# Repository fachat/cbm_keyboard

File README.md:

# Commodore PET keyboards

Note: this is a part of a larger set of repositories, with [upet_family](https://github.com/fachat/upet_family) as the main repository.

This is part of a re-incarnation of the Commodore PET computer(s) from the later 1970s.

This repo shows how to build a keyboard for the Commodore PET, mainly for my own re-incarnation, but potentially for original PET as well (untested).

Keyboards can be seen in the PETindex [keyboard section](http://www.6502.org/users/andre/petindex/keyboards.html).

## N-Type

This keyboard is the typewriter-stlye keyboard used in most 40 column models, except for the originals with the chicklet keyboard.

### PCB

#### Open source PCB by Steve Gray

For my builds I started by using the N-type keyboard PCB by Steve Gray from his [MX replacement keyboards projects](http://cbmsteve.ca/mxkeyboards/index.html)
As Steve only has the PCB, I designed a 3D-printable base support for the PCB.
It is available on tinkercad and the STL files are also available here.

Based on that I created a new R3 version of the board that includes options for
backlit LEDs and keyboard controllers allowing key re-mapping independent from
the PET's own editor ROM. You can find it in [PET-N](PET-N)

NOTE: In R3.0A you need to fix some things:

1. Connect the V33 and VCC33 lines - basically the oscillator for the Atmega controllers does not have power, so that needs to be supplied.
2. There is an off-by-one error on the row multiplexer. It has rows R0-9, while the keys are connected to R1-10. For now you have to connect R0 and R10, and fix the issue in the controller software.

In the current R3.0B these two fixes have been applied, but the actual PCB is not tested yet (and probably never will). A future 3.1 fix this for good.

### Programming the R3 PCB

The R3 PCB has (optionally) two Atmega32a microcontrollers on board, that implement two functions:

1. mapping keys between the keyboard and the host 
2. controlling the LEDs.

To program the Microcontrollers you need an AVR programming tool like the AVRisp MkII that I use, or similar, that can program via the SPI interface (plus Reset) on the 6 pin programming header (which exists separately for each of the two Microcontrollers)

Both microcontrollers are connected to the I2C bus on the extended UPET keyboard interface.

#### Functions of the keyboard controller

Currently the keyboard controller maps the keys 1:1 from the keyboard matrix to the host keyboard interface.

In addition it sends the pressed keys (hardware key index) via I2C to address 0x10 (which is the LED controller).

Also, the keyboard mapping has these options:

1. direct mapping - each key is directly mapped to the corresponding host key
2. The top row of characters is remapped from the PET-N's characters (like $, %, etc) to the digits you'd normally expect in this place. The original chars are available with Shift, the originally shifted characters are available with Ctrl.

Note that in the future more mappings may be implemented.

Selection of the mapping is done by pressing the SRQ key a few seconds long. The keyboard will then send a menu text to the host that instructs the user how to switch the mapping.
It is best if the menu is triggered e.g. on the BASIC prompt.

The mapping is stored in the Atmega's EEPROM, and thus retained when the machine is switched off.

#### Functions of the LED controller

The LED controller listens on the I2C address 0x10 for commands.

With these commands you can set the constant value of each key LED, but also trigger certain programs that involve either a single key, or multiple keys.
For single keys you can let the colour slowly get dimmer until the LED is off, and then optionally restart with the original value.

The DILUTE program tries to do a simulated flow of the colour from the given key to the surrounding keys. It is not as good and smooth as it could be as the 
Atmega lacks memory to store the required precision of colour values.

The LOGO just sends the logo onto the keypad, and then lets it decay.

```
        // single LED programs. Followed by index, three colours, and a parameter
        LP_CONST        = 0,    // constant value, using the three parameters as RGB
        LP_LINDECAY     = 1,    // linear decay (note may change hue while getting lower)
        LP_LINDECAYLOOP = 2,    // linear decay with restart

        // single command program
        SP_KEYPRESS     = 64,   // just followed by the index to indicate a pressed key

        // multi-key programs
        KP_DILUTE       = 128,  // set initial value to given params, then let it flow off 
        KP_LOGO         = 129,  // C= logo on the keypad
```

All commands except KEYPRESS expect the key index, three colours, and a parameter after the command, i.e. six bytes in total.
KEYPRESS only has the index and thus requires only two bytes.

### Supports for PCB

The PCB needs some kind of support to be mounted into the PET or the Ulti-/Micro-PET cases.
There are two versions for Steve's and my derived PCB, the first one for the extended
that caters for the different connector, and the one better suitable for the original
PCB.

* [New support structure extended PET-N keyboard](https://www.tinkercad.com/things/2KwSQVdno7K-sjg-keybd-full-support-r1)
* [left part of the support](PET-Keyboard-Support-SJG-N-R1-left.stl)
* [right part of the support](PET-Keyboard-Support-SJG-N-R1-right.stl)

* [support structure for Steve's N-type keyboard at tinkercad](https://www.tinkercad.com/things/cUVlushPB3j-sjg-keybd-full-support-v07).
* [left part of the support](PET-Keyboard-Support-SJG-N-v07-left.stl)
* [right part of the support](PET-Keyboard-Support-SJG-N-v07-right.stl)

#### Texelec Petskey keyboard

This is the PET N-type keyboard available from Texelec.

As this is the PCB only, I have created a support structure for this too. Note, however, as I now prefer Steve's PCB, I only have an old version of the supports on tinkercad.

Two of each of these supports make up a keyboard base plate, where you only need to clip in the PCB for the keyboard with the mounted key switches. Then they have about the same dimensions as a C64 keyboard, and you can use them on top of the C64 keyboard support stands.

* [Petskey 1.0 keyboard on Texelec](https://texelec.com/product/petskey/)
* [Petskey support on tinkercad](https://www.tinkercad.com/things/5lenSoehSRu-petskey-full-support-plate)

### Key caps

There are two options, either use standard key caps, or 3D-printed ones.

#### Standard Keycaps

As, for the self-built keyboards from option 1 or 2 some standard MX switches are used, standard
key caps can be used as well. There is one caveat, however.

Newer key caps typically have a different inclination for each row of keys, that is the angle of the top key surface against the horizontal
is different for each row. This is to facilitate easier typing. In fact even the C64 keyboard has this.
The old PET keyboards, however, have the same angle - which is not zero! - for all rows. This makes it easier to use the same cap (in terms of physical dimensions)
on all rows, and just print on a different character for each key. Read more on those [key profiles](https://switchandclick.com/sa-vs-dsa-vs-oem-vs-cherry-vs-xda-keycap-profiles/).

I used two type of standard key caps:

1. [XDA profile, unmarked](https://www.amazon.de/gp/product/B06XSHK528/): this set of key caps does not have a print on it, and all keys have the same angle - zero. So it is
possible to use any of the key caps in any row. Which is important, as you need a specific number of keys for each key width.
Also, this set has space bars in different lengths, and there is one that fits the 6.25 character wide space bar for the petskey and sjg keyboards.
For the markings I just used a pen...

2. This one [Glorious PC Gaming Race ABS Doubleshot black, ANSI layout GAKC-045](https://www.caseking.de/glorious-pc-gaming-race-abs-doubleshot-schwarz-ansi-us-layout-gakc-045.html) I actually bought more or less
by accident. I only noticed that it has different angles per row when I tried it out. However, with the amount of caps I was able to only
use a wrong angle on Shift Lock, left Shift, Return and "4" - but it's barely noticable.
For the markings I used template from Steve's page, printed it on sticky paper, cut it out and glued it on the keys where the original did not fit.

#### Printed Keycaps

As a third option I used 3-D printed key caps that I designed myself.

The keycaps are made of three parts each:
1) a key form created by a parametric generator,
2) the top character print, extruded from the key form,
3) the front character (mostly the shifted character), extruded from the key form.

I created all parts, and integrated them in the [Tinkercad](https://tinkercad.com) web tool.

The key form is created using OpenSCAD by a [parametric generator](https://www.thingiverse.com/thing:2783650) (by Thingieverse user rsheldiii, published under the [CC BY-SA 3.0](https://creativecommons.org/licenses/by-sa/3.0/) license). Here is the [parameter file](keycaps/key_cbm3_customizer.scad). Only the key width needs to be adapted, and the inversion of the top for the space key.

Most of the top character prints are made from a [Microgramm font](https://www.wfonts.com/font/microgramma), converted to SVG using the [Font Squirrel](https://www.fontsquirrel.com/tools/webfont-generator) web page.

Some top characters, and especially the top words ("SHIFT", "RUN STOP" etc) are taken from [Steve's github page](https://github.com/sjgray/CBM-MX-Keyboards/tree/master/stickers). As SVG exported from inkscape did not work when imported
into tinkercad, I had to make screenshots from each character, and convert these screenshots into SVGs using this [online converter](https://image.online-convert.com/convert-to-svg).

The front characters are all from an [SVG file from wikipedia](https://en.wikipedia.org/wiki/Commodore_PET#/media/File:PET_Keyboard_improved.svg), from which I also took screenshots and converted to SVG as above.

You can find an oder version of the the STL files [here](keycaps/), in four parts due to its size. The current version is linked from tinkercad below.
Please note that it took me about 100+ hours just to print the full set of keys on my Snapmaker printer in high quality.
After printing you have to remove the supports that anchor the stem to the outside of the keycaps so it does
not break away when printing.

For your convenience there is an open project at PCBWay to print the key caps, see the links.

* [Keycaps for resin printing](https://www.tinkercad.com/things/7a94wJbLJPW-commodore-pet-caps-for-n-type-ulti-keyboard-resin?sharecode=oM7332wY6SwB6DUj0fZoZttCZ-khZDpZEqtmBmInKJo)
* [Master file for keycaps](https://www.tinkercad.com/things/clKxMCUccgg-master-commodore-pet-caps-for-n-ulti-keyboard-support-cuts)
[//] # * [Open project at PCBWay 3D printing](https://www.pcbway.com/project/shareproject/Commodore_PET_N_type_keycaps_c1c2d1a0.html)

### Switches

The PCBs work with standard Cherry-type/-compatible switches. I only tested Cherry brand switches, though. You may select depending on your preference regarding force needed, click noise etc.

I found the MX1A-C1NW a good compromise for me.

* [Cherry MX1A-C1NW at Mouser](https://www.mouser.de/ProductDetail/540-MX1A-C1NW)

## Gallery

 Assembled keyboard with white resin printed caps, with key prints painted with black alcohol ink
 Assembled keyboard with black PLA printed caps, with key prints painted with white alcohol ink
 Assembled keyboard with black PLA printed caps

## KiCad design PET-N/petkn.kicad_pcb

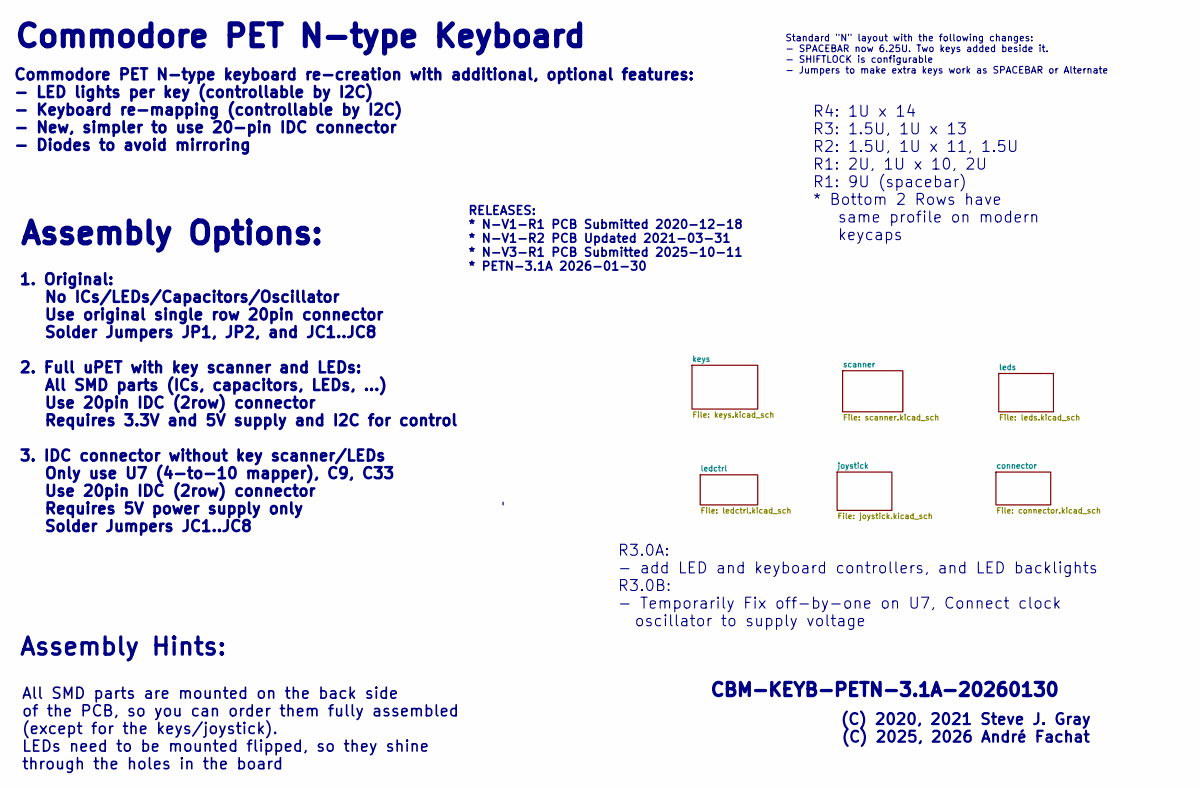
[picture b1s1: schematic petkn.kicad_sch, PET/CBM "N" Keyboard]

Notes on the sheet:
1. Original: No ICs/LEDs/Capacitors/Oscillator Use original single row 20pin connector Solder Jumpers JP1, JP2, and JC1..JC8 2. Full uPET with key scanner and LEDs: All SMD parts (ICs, capacitors, LEDs, ...) Use 20pin IDC (2row) connector Requires 3.3V and 5V supply and I2C for control 3. IDC conne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
R3.0A: - add LED and keyboard controllers, and LED backlights R3.0B: - Temporarily Fix off-by-one on U7, Connect clock oscillator to supply voltage
All SMD parts are mounted on the back side of the PCB, so you can order them fully assembled (except for the keys/joystick). LEDs need to be mounted flipped, so they shine through the holes in the board
Commodore PET N-type keyboard re-creation with additional, optional features: - LED lights per key (controllable by I2C) - Keyboard re-mapping (controllable by I2C) - New, simpler to use 20-pin IDC connector - Diodes to avoid mirroring
Assembly Options:
RELEASES: * N-V1-R1 PCB Submitted 2020-12-18 * N-V1-R2 PCB Updated 2021-03-31 * N-V3-R1 PCB Submitted 2025-10-11 * PETN-3.1A 2026-01-30
(C) 2020, 2021 Steve J. Gray (C) 2025, 2026 André Fachat
R4: 1U x 14 R3: 1.5U, 1U x 13 R2: 1.5U, 1U x 11, 1.5U R1: 2U, 1U x 10, 2U R1: 9U (spacebar) * Bottom 2 Rows have same profile on modern keycaps
Assembly Hints:
Commodore PET N-type Keyboard
Standard "N" layout with the following changes: - SPACEBAR now 6.25U. Two keys added beside it. - SHIFTLOCK is configurable - Jumpers to make extra keys work as SPACEBAR or Alternate
CBM-KEYB-PETN-3.1A-20260130

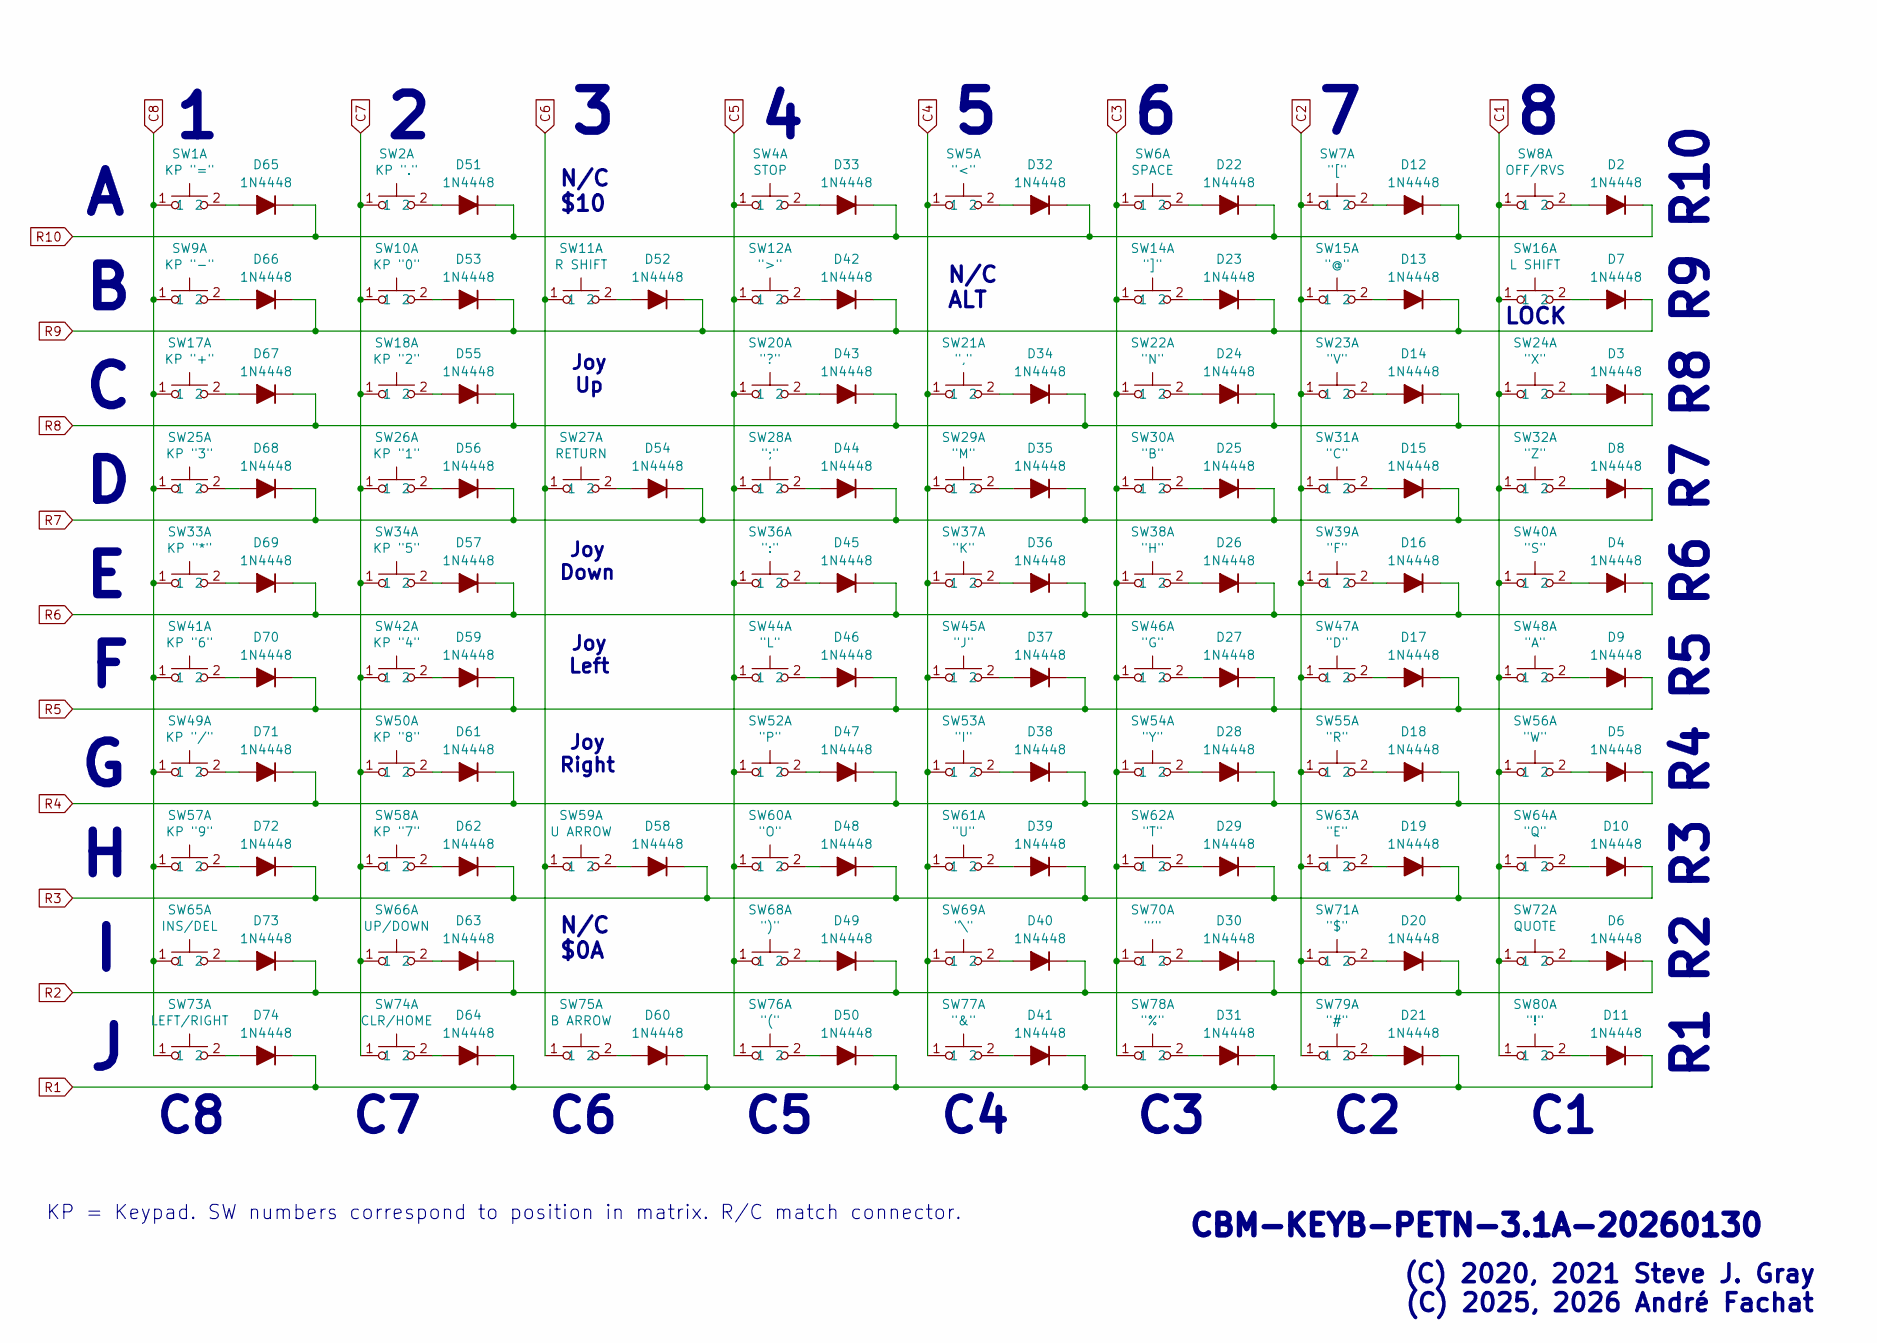
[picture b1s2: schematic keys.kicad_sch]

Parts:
D2, D3, D4, D5, D6, D7, D8, D9, D10, D11, D12, D13, D14, D15, D16, D17, D18, D19, D20, D21, D22, D23, D24, D25, D26, D27, D28, D29, D30, D31, D32, D33, D34, D35, D36, D37, D38, D39, D40, D41, D42, D43, D44, D45, D46, D47, D48, D49, D50, D51, D52, D53, D54, D55, D56, D57, D58, D59, D60, D61, D62, D63, D64, D65, D66, D67, D68, D69, D70, D71, D72, D73, D74: 1N4448; D_SOD-323_HandSoldering
SW1: KP "="; SW_Cherry_MX_1.00u_PCB_with_RGB_LED
SW2: KP "."; SW_Cherry_MX_1.00u_PCB_with_RGB_LED
SW4: STOP; SW_Cherry_MX_1.00u_PCB_with_RGB_LED
SW5: "<"; SW_Cherry_MX_1.00u_PCB_with_RGB_LED
SW6: SPACE; SW_Cherry_MX_6.25u_PCB_with_RGB_LED
SW7: "["; SW_Cherry_MX_1.00u_PCB_with_RGB_LED
SW8: OFF/RVS; SW_Cherry_MX_1.50u_PCB_with_RGB_LED
SW9: KP "-"; SW_Cherry_MX_1.00u_PCB_with_RGB_LED
SW10: KP "0"; SW_Cherry_MX_1.00u_PCB_with_RGB_LED
SW11: R SHIFT; SW_Cherry_MX_2.00u_PCB_with_RGB_LED
SW12: ">"; SW_Cherry_MX_1.00u_PCB_with_RGB_LED
SW14: "]"; SW_Cherry_MX_1.00u_PCB_with_RGB_LED
SW15: "@"; SW_Cherry_MX_1.00u_PCB_with_RGB_LED
SW16: L SHIFT; SW_Cherry_MX_2.00u_PCB_with_RGB_LED
SW17: KP "+"; SW_Cherry_MX_1.00u_PCB_with_RGB_LED
SW18: KP "2"; SW_Cherry_MX_1.00u_PCB_with_RGB_LED
SW20: "?"; SW_Cherry_MX_1.00u_PCB_with_RGB_LED
SW21: ","; SW_Cherry_MX_1.00u_PCB_with_RGB_LED
SW22: "N"; SW_Cherry_MX_1.00u_PCB_with_RGB_LED
SW23: "V"; SW_Cherry_MX_1.00u_PCB_with_RGB_LED
SW24: "X"; SW_Cherry_MX_1.00u_PCB_with_RGB_LED
SW25: KP "3"; SW_Cherry_MX_1.00u_PCB_with_RGB_LED
SW26: KP "1"; SW_Cherry_MX_1.00u_PCB_with_RGB_LED
SW27: RETURN; SW_Cherry_MX_1.50u_PCB_with_RGB_LED
SW28: ";"; SW_Cherry_MX_1.00u_PCB_with_RGB_LED
SW29: "M"; SW_Cherry_MX_1.00u_PCB_with_RGB_LED
SW30: "B"; SW_Cherry_MX_1.00u_PCB_with_RGB_LED
SW31: "C"; SW_Cherry_MX_1.00u_PCB_with_RGB_LED
SW32: "Z"; SW_Cherry_MX_1.00u_PCB_with_RGB_LED
SW33: KP "*"; SW_Cherry_MX_1.00u_PCB_with_RGB_LED
SW34: KP "5"; SW_Cherry_MX_1.00u_PCB_with_RGB_LED
SW36: ":"; SW_Cherry_MX_1.00u_PCB_with_RGB_LED
SW37: "K"; SW_Cherry_MX_1.00u_PCB_with_RGB_LED
SW38: "H"; SW_Cherry_MX_1.00u_PCB_with_RGB_LED
SW39: "F"; SW_Cherry_MX_1.00u_PCB_with_RGB_LED
SW40: "S"; SW_Cherry_MX_1.00u_PCB_with_RGB_LED
SW41: KP "6"; SW_Cherry_MX_1.00u_PCB_with_RGB_LED
SW42: KP "4"; SW_Cherry_MX_1.00u_PCB_with_RGB_LED
SW44: "L"; SW_Cherry_MX_1.00u_PCB_with_RGB_LED
SW45: "J"; SW_Cherry_MX_1.00u_PCB_with_RGB_LED
SW46: "G"; SW_Cherry_MX_1.00u_PCB_with_RGB_LED
SW47: "D"; SW_Cherry_MX_1.00u_PCB_with_RGB_LED
SW48: "A"; SW_Cherry_MX_1.00u_PCB_with_RGB_LED
SW49: KP "/"; SW_Cherry_MX_1.00u_PCB_with_RGB_LED
SW50: KP "8"; SW_Cherry_MX_1.00u_PCB_with_RGB_LED
SW52: "P"; SW_Cherry_MX_1.00u_PCB_with_RGB_LED
SW53: "I"; SW_Cherry_MX_1.00u_PCB_with_RGB_LED
SW54: "Y"; SW_Cherry_MX_1.00u_PCB_with_RGB_LED
SW55: "R"; SW_Cherry_MX_1.00u_PCB_with_RGB_LED
SW56: "W"; SW_Cherry_MX_1.00u_PCB_with_RGB_LED
SW57: KP "9"; SW_Cherry_MX_1.00u_PCB_with_RGB_LED
SW58: KP "7"; SW_Cherry_MX_1.00u_PCB_with_RGB_LED
SW59: U ARROW; SW_Cherry_MX_1.00u_PCB_with_RGB_LED
SW60: "O"; SW_Cherry_MX_1.00u_PCB_with_RGB_LED
SW61: "U"; SW_Cherry_MX_1.00u_PCB_with_RGB_LED
SW62: "T"; SW_Cherry_MX_1.00u_PCB_with_RGB_LED
SW63: "E"; SW_Cherry_MX_1.00u_PCB_with_RGB_LED
SW64: "Q"; SW_Cherry_MX_1.00u_PCB_with_RGB_LED
SW65: INS/DEL; SW_Cherry_MX_1.00u_PCB_with_RGB_LED
SW66: UP/DOWN; SW_Cherry_MX_1.00u_PCB_with_RGB_LED
SW68: ")"; SW_Cherry_MX_1.00u_PCB_with_RGB_LED
SW69: "\"; SW_Cherry_MX_1.00u_PCB_with_RGB_LED
SW70: "'"; SW_Cherry_MX_1.00u_PCB_with_RGB_LED
SW71: "$"; SW_Cherry_MX_1.00u_PCB_with_RGB_LED
SW72: QUOTE; SW_Cherry_MX_1.00u_PCB_with_RGB_LED
SW73: LEFT/RIGHT; SW_Cherry_MX_1.00u_PCB_with_RGB_LED
SW74: CLR/HOME; SW_Cherry_MX_1.00u_PCB_with_RGB_LED
SW75: B ARROW; SW_Cherry_MX_1.00u_PCB_with_RGB_LED
SW76: "("; SW_Cherry_MX_1.00u_PCB_with_RGB_LED
SW77: "&"; SW_Cherry_MX_1.00u_PCB_with_RGB_LED
SW78: "%"; SW_Cherry_MX_1.00u_PCB_with_RGB_LED
SW79: "#"; SW_Cherry_MX_1.00u_PCB_with_RGB_LED
SW80: "!"; SW_Cherry_MX_1.00u_PCB_with_RGB_LED

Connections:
C1: SW8.1, SW16.1, SW24.1, SW32.1, SW40.1, SW48.1, SW56.1, SW64.1, SW72.1, SW80.1; also elsewhere on the board
C2: SW7.1, SW15.1, SW23.1, SW31.1, SW39.1, SW47.1, SW55.1, SW63.1, SW71.1, SW79.1; also elsewhere on the board
C3: SW6.1, SW14.1, SW22.1, SW30.1, SW38.1, SW46.1, SW54.1, SW62.1, SW70.1, SW78.1; also elsewhere on the board
C4: SW5.1, SW21.1, SW29.1, SW37.1, SW45.1, SW53.1, SW61.1, SW69.1, SW77.1; also elsewhere on the board
C5: SW4.1, SW12.1, SW20.1, SW28.1, SW36.1, SW44.1, SW52.1, SW60.1, SW68.1, SW76.1; also elsewhere on the board
C6: SW11.1, SW27.1, SW59.1, SW75.1; also elsewhere on the board
C7: SW2.1, SW10.1, SW18.1, SW26.1, SW34.1, SW42.1, SW50.1, SW58.1, SW66.1, SW74.1; also elsewhere on the board
C8: SW1.1, SW9.1, SW17.1, SW25.1, SW33.1, SW41.1, SW49.1, SW57.1, SW65.1, SW73.1; also elsewhere on the board
unnamed: D2.2 (A), SW8.2
unnamed: D3.2 (A), SW24.2
unnamed: D4.2 (A), SW40.2
unnamed: D5.2 (A), SW56.2
unnamed: D6.2 (A), SW72.2
unnamed: D7.2 (A), SW16.2
unnamed: D8.2 (A), SW32.2
unnamed: D9.2 (A), SW48.2
unnamed: D10.2 (A), SW64.2
unnamed: D11.2 (A), SW80.2
unnamed: D12.2 (A), SW7.2
unnamed: D13.2 (A), SW15.2
unnamed: D14.2 (A), SW23.2
unnamed: D15.2 (A), SW31.2
unnamed: D16.2 (A), SW39.2
unnamed: D17.2 (A), SW47.2
unnamed: D18.2 (A), SW55.2
unnamed: D19.2 (A), SW63.2
unnamed: D20.2 (A), SW71.2
unnamed: D21.2 (A), SW79.2
unnamed: D22.2 (A), SW6.2
unnamed: D23.2 (A), SW14.2
unnamed: D24.2 (A), SW22.2
unnamed: D25.2 (A), SW30.2
unnamed: D26.2 (A), SW38.2
unnamed: D27.2 (A), SW46.2
unnamed: D28.2 (A), SW54.2
unnamed: D29.2 (A), SW62.2
unnamed: D30.2 (A), SW70.2
unnamed: D31.2 (A), SW78.2
unnamed: D32.2 (A), SW5.2
unnamed: D33.2 (A), SW4.2
unnamed: D34.2 (A), SW21.2
unnamed: D35.2 (A), SW29.2
unnamed: D36.2 (A), SW37.2
unnamed: D37.2 (A), SW45.2
unnamed: D38.2 (A), SW53.2
unnamed: D39.2 (A), SW61.2
unnamed: D40.2 (A), SW69.2
unnamed: D41.2 (A), SW77.2
unnamed: D42.2 (A), SW12.2
unnamed: D43.2 (A), SW20.2
unnamed: D44.2 (A), SW28.2
unnamed: D45.2 (A), SW36.2
unnamed: D46.2 (A), SW44.2
unnamed: D47.2 (A), SW52.2
unnamed: D48.2 (A), SW60.2
unnamed: D49.2 (A), SW68.2
unnamed: D50.2 (A), SW76.2
unnamed: D51.2 (A), SW2.2
unnamed: D52.2 (A), SW11.2
unnamed: D53.2 (A), SW10.2
unnamed: D54.2 (A), SW27.2
unnamed: D55.2 (A), SW18.2
unnamed: D56.2 (A), SW26.2
unnamed: D57.2 (A), SW34.2
unnamed: D58.2 (A), SW59.2
unnamed: D59.2 (A), SW42.2
unnamed: D60.2 (A), SW75.2
unnamed: D61.2 (A), SW50.2
unnamed: D62.2 (A), SW58.2
unnamed: D63.2 (A), SW66.2
unnamed: D64.2 (A), SW74.2
unnamed: D65.2 (A), SW1.2
unnamed: D66.2 (A), SW9.2
unnamed: D67.2 (A), SW17.2
unnamed: D68.2 (A), SW25.2
unnamed: D69.2 (A), SW33.2
unnamed: D70.2 (A), SW41.2
unnamed: D71.2 (A), SW49.2
unnamed: D72.2 (A), SW57.2
unnamed: D73.2 (A), SW65.2
unnamed: D74.2 (A), SW73.2
R1: D11.1 (K), D21.1 (K), D31.1 (K), D41.1 (K), D50.1 (K), D60.1 (K), D64.1 (K), D74.1 (K); also elsewhere on the board
R2: D6.1 (K), D20.1 (K), D30.1 (K), D40.1 (K), D49.1 (K), D63.1 (K), D73.1 (K); also elsewhere on the board
R3: D10.1 (K), D19.1 (K), D29.1 (K), D39.1 (K), D48.1 (K), D58.1 (K), D62.1 (K), D72.1 (K); also elsewhere on the board
R4: D5.1 (K), D18.1 (K), D28.1 (K), D38.1 (K), D47.1 (K), D61.1 (K), D71.1 (K); also elsewhere on the board
R5: D9.1 (K), D17.1 (K), D27.1 (K), D37.1 (K), D46.1 (K), D59.1 (K), D70.1 (K); also elsewhere on the board
R6: D4.1 (K), D16.1 (K), D26.1 (K), D36.1 (K), D45.1 (K), D57.1 (K), D69.1 (K); also elsewhere on the board
R7: D8.1 (K), D15.1 (K), D25.1 (K), D35.1 (K), D44.1 (K), D54.1 (K), D56.1 (K), D68.1 (K); also elsewhere on the board
R8: D3.1 (K), D14.1 (K), D24.1 (K), D34.1 (K), D43.1 (K), D55.1 (K), D67.1 (K); also elsewhere on the board
R9: D7.1 (K), D13.1 (K), D23.1 (K), D42.1 (K), D52.1 (K), D53.1 (K), D66.1 (K); also elsewhere on the board
R10: D2.1 (K), D12.1 (K), D22.1 (K), D32.1 (K), D33.1 (K), D51.1 (K), D65.1 (K); also elsewhere on the board

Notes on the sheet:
R1 R2 R3 R4 R5 R6 R7 R8 R9 R10
Joy Up
KP = Keypad. SW numbers correspond to position in matrix. R/C match connector.
Joy Right
LOCK
C8 C7 C6 C5 C4 C3 C2 C1
Joy Down
Joy Left
CBM-KEYB-PETN-3.1A-20260130
N/C $0A
N/C $10
(C) 2020, 2021 Steve J. Gray (C) 2025, 2026 André Fachat
N/C ALT

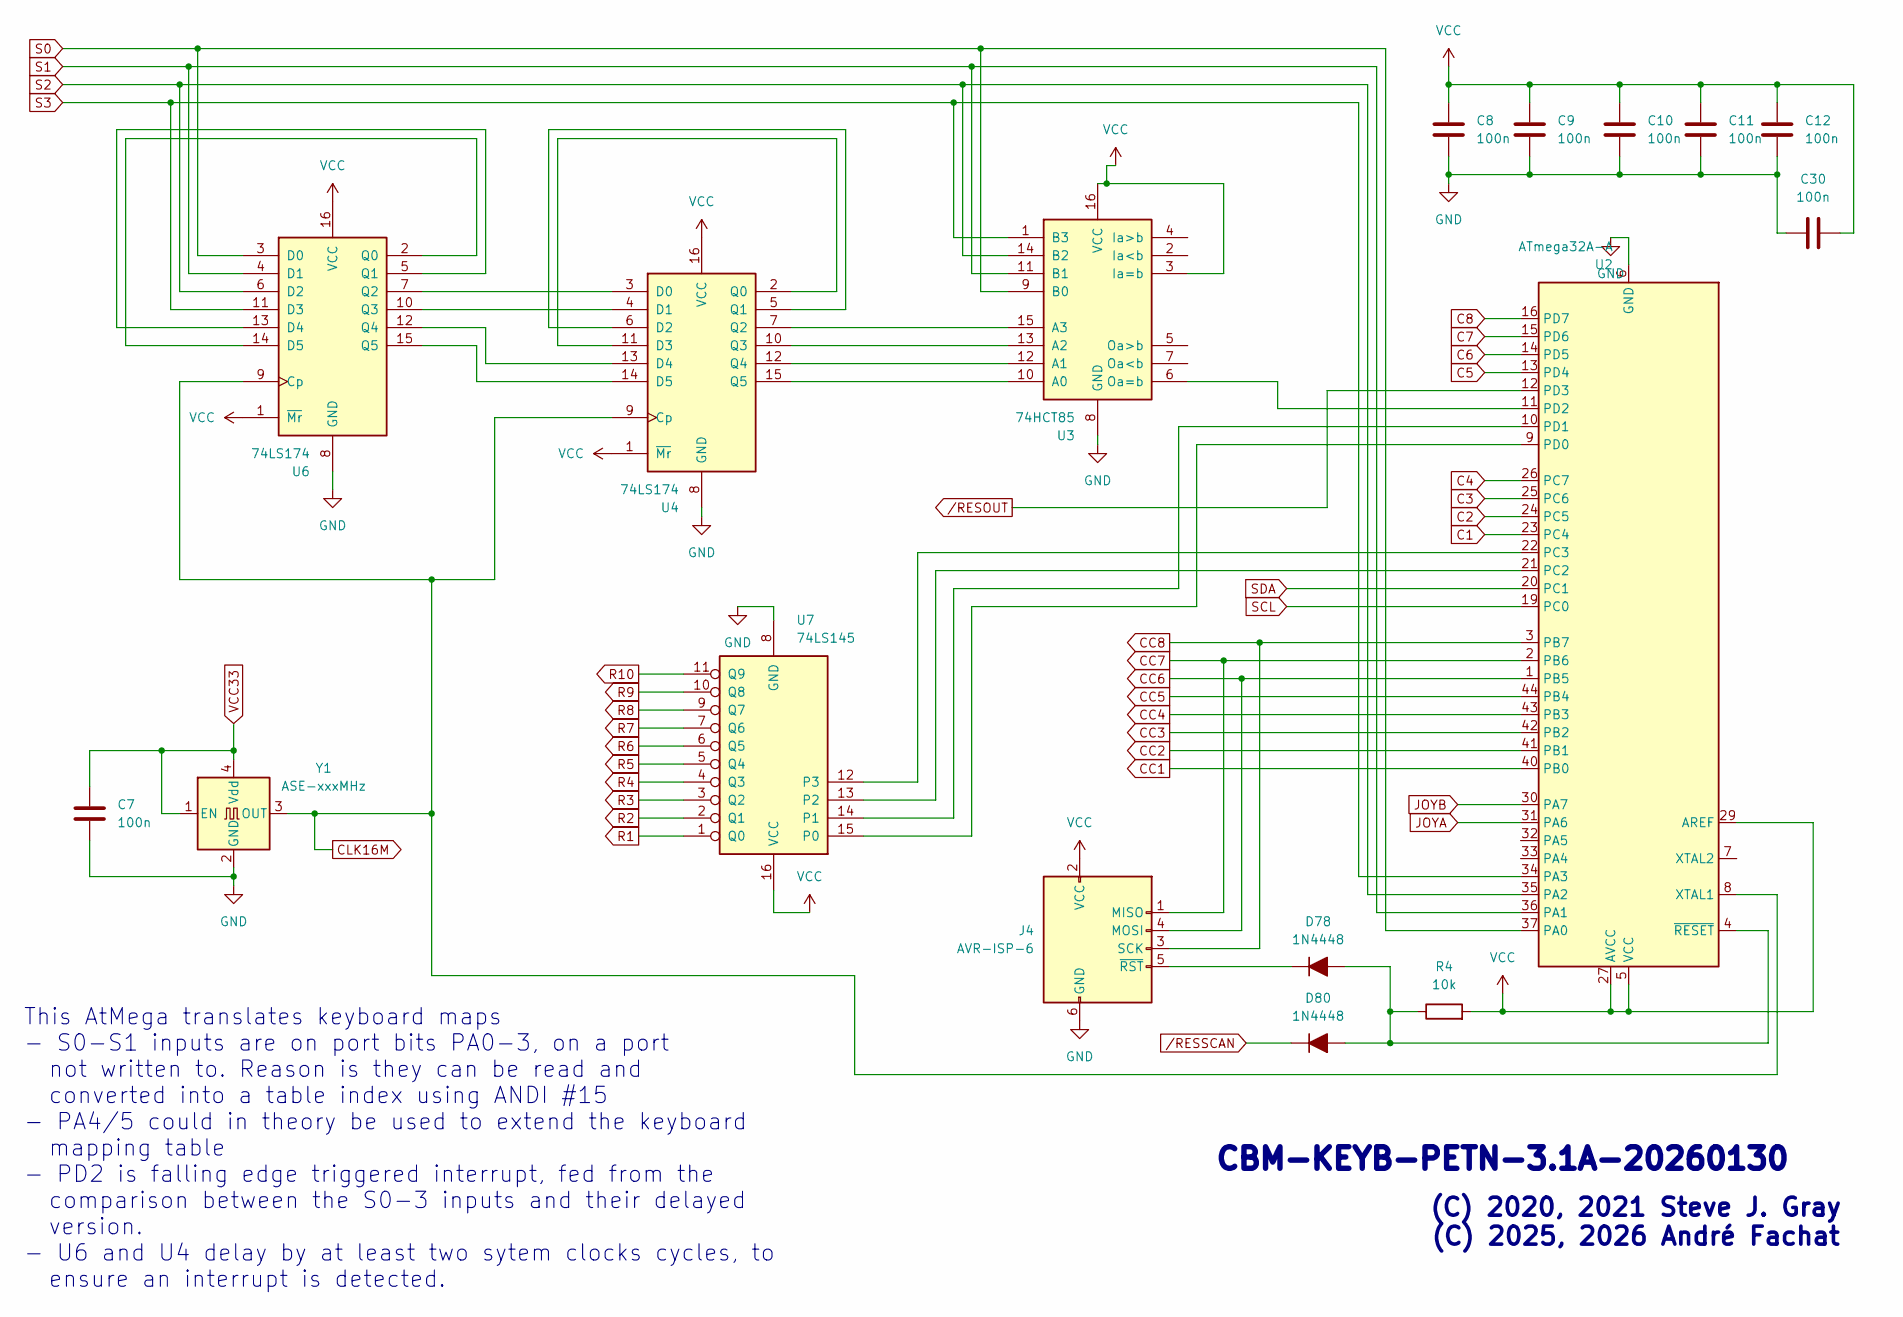
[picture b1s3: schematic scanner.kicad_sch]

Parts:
C7, C8, C9, C10, C11, C12, C30: 100n; C_0805_2012Metric_Pad1.18x1.45mm_HandSolder; LCSC C14663
D78, D80: 1N4448; D_SOD-323_HandSoldering
J4: AVR-ISP-6; IDC-Header_2x03_P2.54mm_Vertical; LCSC C5372863
R4: 10k; R_0603_1608Metric
U2: ATmega32A-A; TQFP-44_10x10mm_P0.8mm; LCSC C5659
U3: 74HCT85; SO-16_3.9x9.9mm_P1.27mm; LCSC C5953
U4, U6: 74LS174; SO-16_3.9x9.9mm_P1.27mm; LCSC C6828
U7: 74LS145; SO-16_3.9x9.9mm_P1.27mm; LCSC C60829
Y1: ASE-xxxMHz; Oscillator_SMD_Abracon_ASE-4Pin_3.2x2.5mm; LCSC C12668

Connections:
C1: U2.23 (PC4); also elsewhere on the board
C2: U2.24 (PC5); also elsewhere on the board
C3: U2.25 (PC6); also elsewhere on the board
C4: U2.26 (PC7); also elsewhere on the board
C5: U2.13 (PD4); also elsewhere on the board
C6: U2.14 (PD5); also elsewhere on the board
C7: U2.15 (PD6); also elsewhere on the board
C8: U2.16 (PD7); also elsewhere on the board
CC1: U2.40 (PB0); also elsewhere on the board
CC2: U2.41 (PB1); also elsewhere on the board
CC3: U2.42 (PB2); also elsewhere on the board
CC4: U2.43 (PB3); also elsewhere on the board
CC5: U2.44 (PB4); also elsewhere on the board
CC6: J4.4 (MOSI), U2.1 (PB5); also elsewhere on the board
CC7: J4.1 (MISO), U2.2 (PB6); also elsewhere on the board
CC8: J4.3 (SCK), U2.3 (PB7); also elsewhere on the board
CLK16M: U2.8 (XTAL1), U4.9 (Cp), U6.9 (Cp), Y1.3 (OUT); also elsewhere on the board
GND: C7.2, C8.2, C9.2, C10.2, C11.2, C12.2, C30.1, J4.6 (GND), U2.6 (GND), U2.18 (GND), U2.28 (GND), U2.39 (GND), U3.8 (GND), U4.8 (GND), U6.8 (GND), U7.8 (GND), Y1.2 (GND); also elsewhere on the board
JOYA: U2.31 (PA6); also elsewhere on the board
JOYB: U2.30 (PA7); also elsewhere on the board
unnamed: D78.2 (A), D80.2 (A), R4.1, U2.4 (~RESET)
unnamed: D78.1 (K), J4.5 (~RST)
unnamed: U2.21 (PC2), U7.13 (P2)
unnamed: U2.22 (PC3), U7.12 (P3)
unnamed: U2.9 (PD0), U7.15 (P0)
unnamed: U2.10 (PD1), U7.14 (P1)
unnamed: U2.11 (PD2), U3.6 (Oa=b)
unnamed: U3.10 (A0), U4.15 (Q5)
unnamed: U3.12 (A1), U4.12 (Q4)
unnamed: U3.13 (A2), U4.10 (Q3)
unnamed: U3.15 (A3), U4.7 (Q2)
unnamed: U4.3 (D0), U6.7 (Q2)
unnamed: U4.4 (D1), U6.10 (Q3)
unnamed: U4.5 (Q1), U4.6 (D2)
unnamed: U4.2 (Q0), U4.11 (D3)
unnamed: U4.13 (D4), U6.12 (Q4)
unnamed: U4.14 (D5), U6.15 (Q5)
unnamed: U6.5 (Q1), U6.13 (D4)
unnamed: U6.2 (Q0), U6.14 (D5)
R1: U7.1 (Q0); also elsewhere on the board
R2: U7.2 (Q1); also elsewhere on the board
R3: U7.3 (Q2); also elsewhere on the board
R4: U7.4 (Q3); also elsewhere on the board
R5: U7.5 (Q4); also elsewhere on the board
R6: U7.6 (Q5); also elsewhere on the board
R7: U7.7 (Q6); also elsewhere on the board
R8: U7.9 (Q7); also elsewhere on the board
R9: U7.10 (Q8); also elsewhere on the board
R10: U7.11 (Q9); also elsewhere on the board
S0: U2.37 (PA0), U3.9 (B0), U6.3 (D0); also elsewhere on the board
S1: U2.36 (PA1), U3.11 (B1), U6.4 (D1); also elsewhere on the board
S2: U2.35 (PA2), U3.14 (B2), U6.6 (D2); also elsewhere on the board
S3: U2.34 (PA3), U3.1 (B3), U6.11 (D3); also elsewhere on the board
SCL: U2.19 (PC0); also elsewhere on the board
SDA: U2.20 (PC1); also elsewhere on the board
VCC: C8.1, C9.1, C10.1, C11.1, C12.1, C30.2, J4.2 (VCC), R4.2, U2.5 (VCC), U2.17 (VCC), U2.27 (AVCC), U2.29 (AREF), U2.38 (VCC), U3.3 (Ia=b), U3.16 (VCC), U4.1 (~Mr), U4.16 (VCC), U6.1 (~Mr), U6.16 (VCC), U7.16 (VCC); also elsewhere on the board
VCC33: C7.1, Y1.1 (EN), Y1.4 (Vdd); also elsewhere on the board
/RESOUT: U2.12 (PD3); also elsewhere on the board
/RESSCAN: D80.1 (K); also elsewhere on the board

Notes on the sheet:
(C) 2020, 2021 Steve J. Gray (C) 2025, 2026 André Fachat
This AtMega translates keyboard maps - S0-S1 inputs are on port bits PA0-3, on a port not written to. Reason is they can be read and converted into a table index using ANDI #15 - PA4/5 could in theory be used to extend the keyboard mapping table - PD2 is falling edge triggered interrupt, fed from t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
CBM-KEYB-PETN-3.1A-20260130

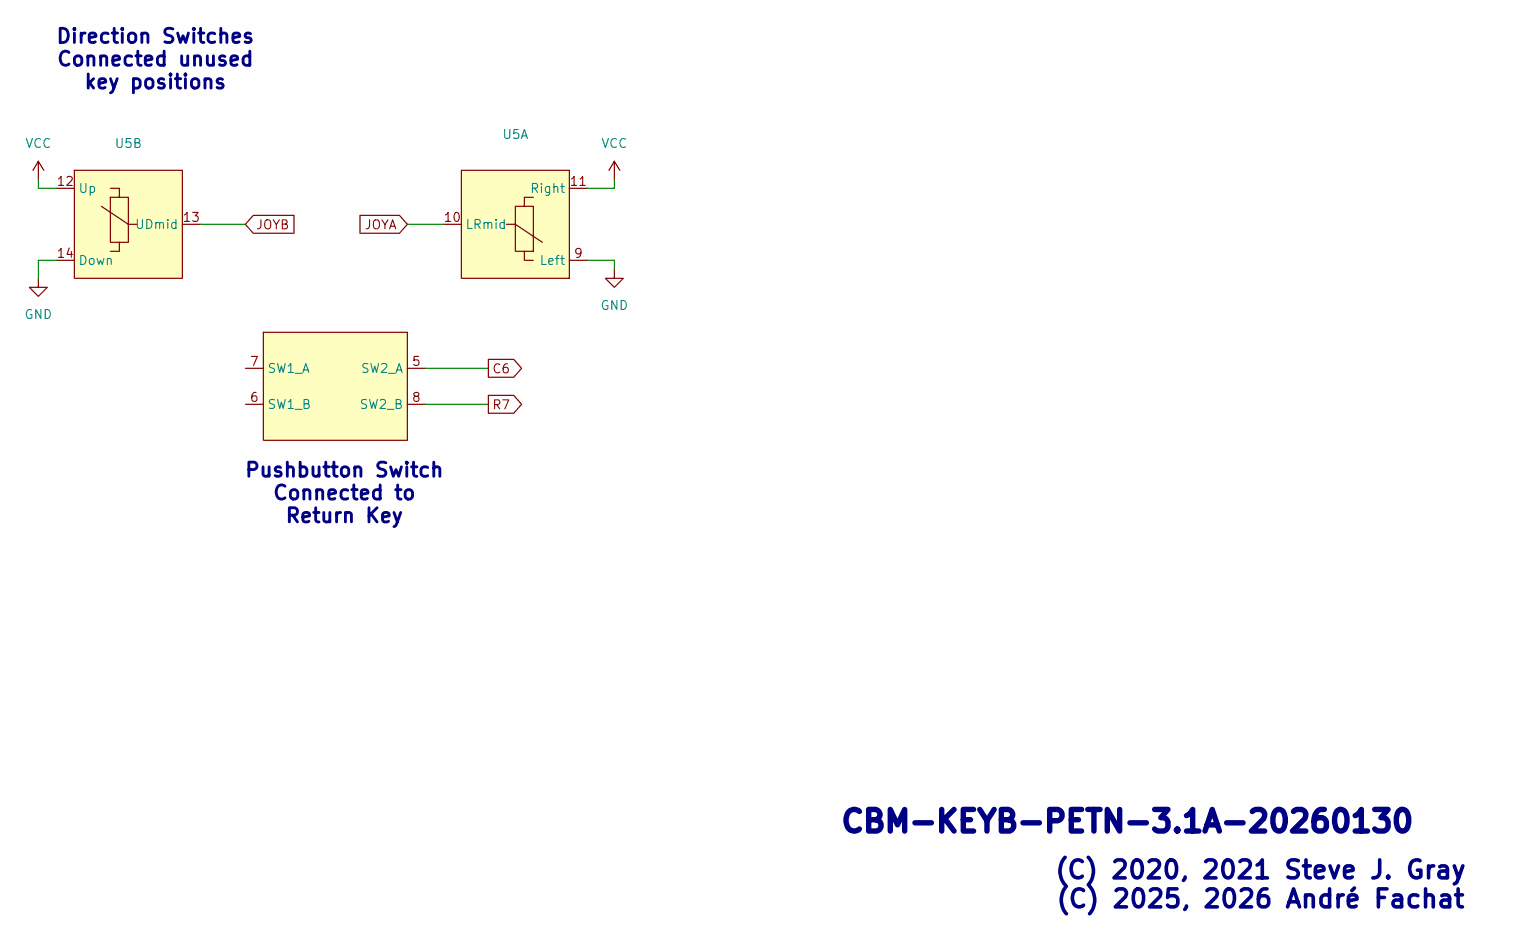
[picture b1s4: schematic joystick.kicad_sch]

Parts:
U5: THB Miniature Thumbstick THB001P; Mouser 611-THB001P

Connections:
C6: U5.5 (SW2_A); also elsewhere on the board
GND: U5.9 (Left), U5.14 (Down); also elsewhere on the board
JOYA: U5.10 (LRmid); also elsewhere on the board
JOYB: U5.13 (UDmid); also elsewhere on the board
R7: U5.8 (SW2_B); also elsewhere on the board
VCC: U5.11 (Right), U5.12 (Up); also elsewhere on the board

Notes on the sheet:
CBM-KEYB-PETN-3.1A-20260130
Pushbutton Switch Connected to Return Key
(C) 2020, 2021 Steve J. Gray (C) 2025, 2026 André Fachat
Direction Switches Connected unused key positions
